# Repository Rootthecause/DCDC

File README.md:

Dear Formula Student Teams,

I've designed a High Voltage DC/DC Converter to replace our LV Battery. Feel free to use it as well!<br>
Although this design (and previous versions) have passed two times FSG scrutineering and have been operating without any issues for over 6 months, <strong>always manufacture at your own risk!</strong><br>
If you encountered any bugs or have suggestions for improvement, please use the GitHub [issues form](https://github.com/Rootthecause/DCDC/issues/new). For discussions and technical questions, kindly use the [discussion bord](https://github.com/Rootthecause/DCDC/discussions).<br> 

This design is published as open-source hardware under the CERN-OHL-W license and can be found on GitHub: https://github.com/Rootthecause/DCDC<br>
If you had early access to this GitHub page or received any files from me directly, please do not share or publish them, as I don't want others to share files which may be incomplete or contain errors.<br>

Have fun! Do not lick things with spark symbols on :) 

Best regards,
Rootthecause / Liv 

March 10, 2026: Thanks for giving this repro more than 100 stars! ⭐️
<br>

# Updates
### For recent updates on building a v9-3 replica, please read [the v9-3 Build Notes](https://github.com/Rootthecause/DCDC/blob/main/v9-3_build_notes.md).

|Date YYMMDD| Description |
|:---------------------:|:------|
|260812|**Urgent notice:** The distance between F1 and RV1 is too small, which can lead to a arc on the HV side while the DCDC is enabled. As long as both components do not touch each other conformal coating would prevent the insulation fault, however the actual spacing is influenced by mechanical tolerances. As a hotfix, isolating glue can be used to fill the gap and/or [low profile fuse clips](https://www.mouser.de/de/ProductDetail/576-01220090Z) (currently untested, should be less wide). The current spacings on the top copper layer between the components are sufficinet with conformal coating. More details on this issue will be added to the Build Notes soon.|
|260730| Currently used resonant C0G capacitors might cause converter failures. See [v9-3 Build Notes](https://github.com/Rootthecause/DCDC/blob/main/v9-3_build_notes.md) for more details.| 
|260609| Added new [v9-4_dev](https://github.com/Rootthecause/DCDC/tree/v9-4_dev) branch. This version is currently untested and not recommended for use. Some components were improved, like D14, U1, U11, Q8, Q9, Q10, Q11. SR FETs have more vias and 20% larger cooling surface. Increased TS side control voltage from 12V to 15V for lower conduction losses.|
|260326 | Update on [v10 development](https://github.com/Rootthecause/DCDC/discussions/9#discussioncomment-16319278) currently being slowed down due to transformer issues.|
|260314| Release of the v9-3r1.4 update. Fixes many smaller issues and probably issue #10. See [releases](https://github.com/Rootthecause/DCDC/releases) for more details.|
|260129| First public v10 schematic, see [v10 development](https://github.com/Rootthecause/DCDC/discussions/9#discussioncomment-15634156), also contains a timeline and small v9-3 update|
|260104| New year's update on [v10 development](https://github.com/Rootthecause/DCDC/discussions/9#discussioncomment-15400450) |
|251130| Update on [v10 development](https://github.com/Rootthecause/DCDC/discussions/9#discussioncomment-15114408), added  for faster communication.|
|250915| **IMPORTANT NOTICE**: There was a complaint about the converter not being rules conform. Due to other personal priorities it might take some weeks to solve the addressed points. There is also the chance of some points unable to be resolved for the Version 9-3r. See [issue#10](https://github.com/Rootthecause/DCDC/issues/10) for further details.|
|250806| Announcing the v10 development - ideas welcome! Read more [here](https://github.com/Rootthecause/DCDC/discussions/9). DCDCv10 [survey](https://forms.gle/ou8AZbYJj4cU9K3A8).|
|250718| A bad F_min setting lead to repeatable FET destruction, please re-read the Build Guide Pages 35/36 if you've set up your replica before this change. See [issue#8](https://github.com/Rootthecause/DCDC/issues/8) |
<br>

# Important documents
|File | | |
|:---------------------:|:--------------:|:------:|
| Documentation [PDF] | [ENGLISH](https://github.com/Rootthecause/DCDC/blob/main/documentation/Documentation_DCDCv9-3r_EN.pdf)| [GERMAN](https://github.com/Rootthecause/DCDC/blob/main/documentation/Documentation_DCDCv9-3r_GER.pdf) [Discontinued*]|
| Build Guide [PDF] | [ENGLISH](https://github.com/Rootthecause/DCDC/blob/main/documentation/Build_Guide_DCDCv9-3r_EN.pdf)| [GERMAN](https://github.com/Rootthecause/DCDC/blob/main/documentation/Build_Guide_DCDCv9-3r_GER.pdf) [Discontinued*]|
| Data sheet [PDF] | [ENGLISH](https://github.com/Rootthecause/DCDC/blob/main/documentation/Datasheet_DCDCv9-3.pdf)|-|
| KiCAD Files| [ENGLISH](https://github.com/Rootthecause/DCDC/tree/main/kicad)|-|
| Schematic [PDF] | [ENGLISH](https://github.com/Rootthecause/DCDC/blob/main/kicad/DCDCv9-3.pdf) |-|
| LTspice Simulation| [ENGLISH](https://github.com/Rootthecause/DCDC/tree/main/ltspice)|-|
| Measurements Table [xlsx] | [ENGLISH](https://github.com/Rootthecause/DCDC/blob/main/documentation/DCDCv9-3_Table.xlsx) |-|
| Scrutineering Support Presentation [PPTX] | [ENGLISH](https://github.com/Rootthecause/DCDC/blob/main/documentation/scrutineering_support_files/DCDCv9-3_Scrutineering_Support_Presentation.pptx)|-|

*will not be updated after the DCDCv9-3r1.4 release (March 14, 2026).

<br>

# Note for PCB-Orders
**Always check the latest release before ordering!**
There are new releases for every significant hardware change.
I do not recommend ordering from the latest repro clone, as it might contain unfinished hardware changes. However, simulation files or documents might be more recent.
<br>
<br>
# Who should build this?
This project is for anyone who is keen to build a DC/DC converter for powering low voltage devices from high voltages or for research.
Unfortunately, it's currently not a simple one-day-build (maybe 1-2 days for building and 1-2 Weeks for testing), but I'm working on it, making it as accessible as possible.
The skillset required ranges from soldering SMD components, SLA-Printing to sanding ferrite cores and winding a transformer (sanding is currently not needed anymore).
The documentation not only contains explanations of many components, but also detailed written assembly instructions.
I might also record a few instruction videos if there is a demand.
Stick with it - the results speak for themselves.<br>
<br>
# Technical Specifications

The DCDCv9-3 is a galvanically isolated DC/DC converter, designed to convert voltages from 200 V to 600 V down to 24 V with max. 500 W continuous output power. The low weight of 167 grams and the small footprint of a credit card (85.6 x 54 mm) are well suited to the automotive industry for supplying low-voltage systems from HV Batteries. The dynamic operating frequency between 90 and 200 kHz ensures high efficiency for various loads as well as good EMI compliance due to the resonant LLC soft switching topology. Customized versions allow output voltages from 12 V to 48 V.
<strong>

- Input Voltage Range: 200 to 600 V 
- Designed Output Voltage: 24 V
- max. Output Power (min. 400V):
	- Continous:&ensp;&ensp;&ensp;&ensp;500 W
	- 180 Seconds:&ensp; 600 W
	- 60 Seconds:&ensp;&ensp;&ensp;750 W
- max. continous Output Power at 200V: 300 W
- max. continous Output Power at 300V: 500 W
- Efficiency up to 96.9 % at 500 W load / 500 V input
- Size: 85.6 x 54 mm x 45 mm
- Weight: 167 grams

Features
- built-in solid-state precharge
- active rectification (NCP4305DMTTWG)
- Galvanically isolated enable pins with self recharging start-up capacitor
- undervoltage, overvoltage and overcurrent protection 
- low no-load power dissipation (7W-9W) 
- cost efficient UCC25600 LLC controller
- reliable 4 A/6 A UCC21520 Gate Driver
- onboard HV- and LV fuses
- minimum isolation distance 4.5 mm (According to rule EV 4.3.6, Table 5, Conformal Coating: 600V DC -> min. 4 mm spacing required)
- optional back side connectors for on-PCB mount 
- "FSG-Rules 2026 v1.1 conform", the complaint #10 was resolved in the v9-3r1.4 release. Teams were able to pass at FSCH, FSA, FSCZ in 2026 [more to come]. NOTE: As converters are manufactured by the teams with individual components (such as the HF-litz wire), they must be able to show e.g. isolation ratings. Without this, passing the technical inspection may be at the discretion of the scrutineer.
</strong>
<br>
<br>

### Future plans

The main goal of this project is to create a universal approach for safe and efficient conversion of voltages.
At the moment, the converter can accept any input voltage up to at least 600V if UVP/OVP and component
Values are chosen correctly. On the output side, the step-down regulator (65V) is the limiting factors. 
A VIPER06 IC could be used to achieve HV stepdown, or depending on the input voltage, 
the stepdown could be could be shifted to the input side. This could also allow a self-starting converter to 
be used as an SMPS in combination with a PFC. Another approach would be a bidirectional design so that the 
stepdown is on the lower voltage side. Since active rectification is already implemented, bidirectional 
conversion could be possible given the right IC. With the current development and rise of GaN MOSFETs, 
a converter with PCB transformer in the MHz range might also be possible.

# Do's and dont's 
## General
- Not as much as possible, but as much as needed (words from a friend).
- If you don't test to the limits, you don't know where they are.
- Always start with low Voltage/Power and slowly increase it.
- Figure out what measurements and values (step size) are important.
- If issues appear, try to solve them sooner than later - but depending on type, they can be an oppurtunity to test out limits.
- avoid making too many changes at once (except you want to perform multivariant testing), or be sure that the changes do not affect each other

## Project specific
- use short traces for anything that has to switch things (PCB design is complex, than that, but keep wire impedance low as well as parasitics)
- make sure, your gate Driver provides clean on-off signals to the MOSFETs. Otherwise you'll blow them up for sure sooner or later. Use MOSFETs with Kelvin connections if possible (and be sure about their correct wiring).
- Do use Gate driver IC's and not Gate Transformes (they suck). If possible, use Isolated Gate Drivers. Thats a good layer of protection if the half bridge blows up.
- Always have a Thermal Camera at hand. There are relatively cheap options as USB-C accessories for Phones (~250€). I use one from TOPDON with an added maco lens. It's worth every penny, not just for a DC/DC but also other FS Stuff. It will help you to find overloaded components (too hot) or non functioning compontens (no heat). Keep in mind, that there might be thermally reflective surfaces (brushed aluminium is like a mirror!). 
- Use your ears and nose in a quite environment while testing. Many issues can be heard (humming, cracking sounds), and some smelled (too hot component).
- Be sure to add test points to your PCB while developing, which can be acessed via jumper wires or simliar. Do not attempt to measure anything directly with a probe while the converter is running, since a small slip can be enough to ruin the whole converter and maybe even do harm to yourself. 
- use an Oscilloscope with Isolated inputs (alternative use differential probes or an battery powered Oscilloscope) to check signals. 

## Replicas
*Last updated: June 24, 2026*

- At least 4 Formula Student teams are replicating the DCDCv9-3r in 2026  
- At least 4 teams have successfully built and tested the DCDCv9-3r:  
  - TU Graz Racing, Austria, 2025 + 2026
  - Anonymous team, Germany, 2025
  - Anonymous team, Czech, 2025
  - Anonymous team, (modified version), England, 2026
  - Arrabona Racing Team, Hungary, 2026 
<br>

**Want to add your team to this list (publicly or anonymously)?**  
Send me a DM on [Reddit](https://www.reddit.com/user/Rootthecause/). 
Thanks! <br>

## Star History

<a href="https://www.star-history.com/?type=date&legend=bottom-right&repos=Rootthecause%2Fdcdc">
 <picture>
   <source media="(prefers-color-scheme: dark)" srcset="https://api.star-history.com/chart?repos=Rootthecause/dcdc&type=date&theme=dark&legend=bottom-right&sealed_token=mzjVnRIkla1vRBk2-KK44TFHBLLXQNpQxWfrkvZrKnmeYRq4vDsalk-4ebVN9e_loyW0JTCKtIhzX2gAzmecnIZoZ-mtmyZheD50UHvruGQUZOgHEQh1tdMgoWUtcaJrPUCjxlboJflvB1i19gqI4QuvRyrbwL13nwhyrt8bHj4ZewdpJkWvTW374E3O" />
   <source media="(prefers-color-scheme: light)" srcset="https://api.star-history.com/chart?repos=Rootthecause/dcdc&type=date&legend=bottom-right&sealed_token=mzjVnRIkla1vRBk2-KK44TFHBLLXQNpQxWfrkvZrKnmeYRq4vDsalk-4ebVN9e_loyW0JTCKtIhzX2gAzmecnIZoZ-mtmyZheD50UHvruGQUZOgHEQh1tdMgoWUtcaJrPUCjxlboJflvB1i19gqI4QuvRyrbwL13nwhyrt8bHj4ZewdpJkWvTW374E3O" />
   
 </picture>
</a>
<br>
<br>

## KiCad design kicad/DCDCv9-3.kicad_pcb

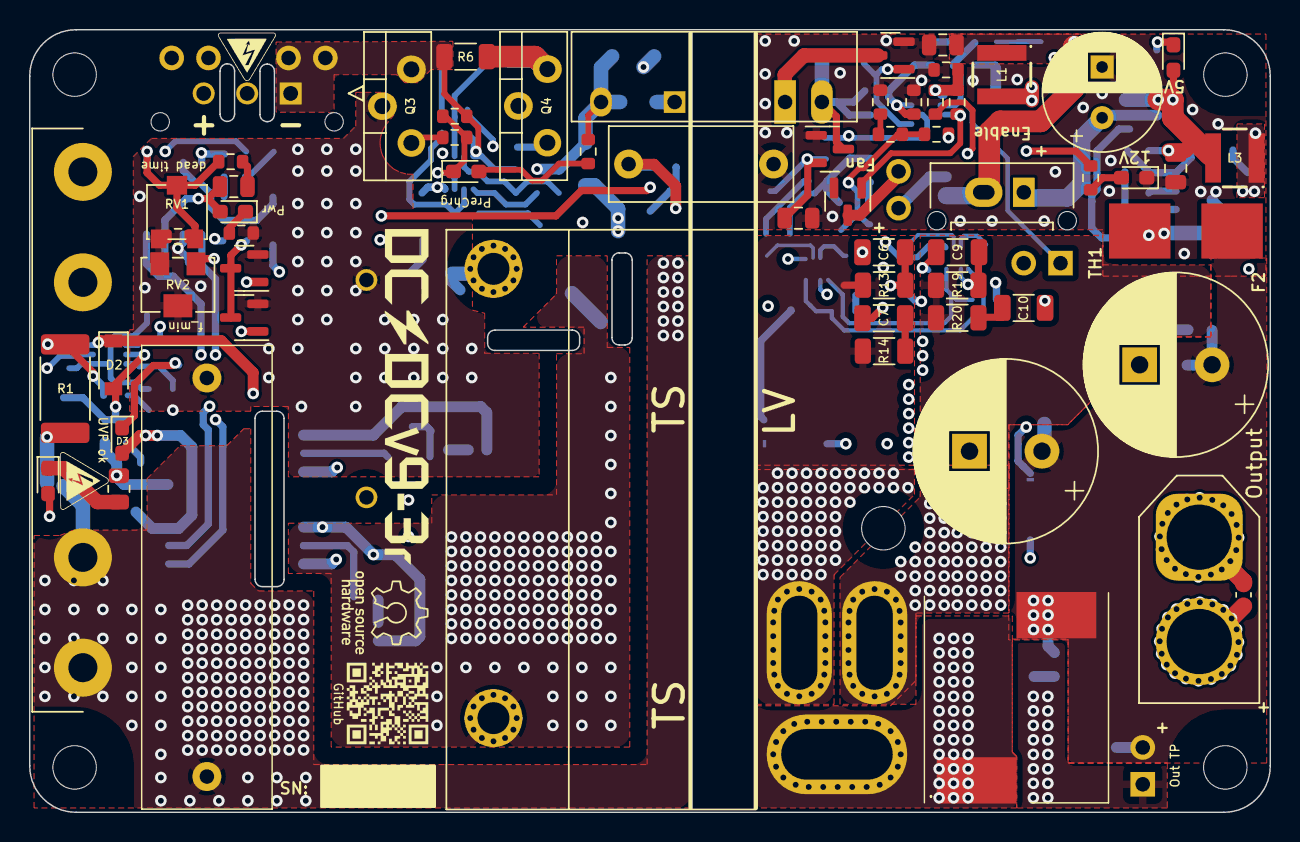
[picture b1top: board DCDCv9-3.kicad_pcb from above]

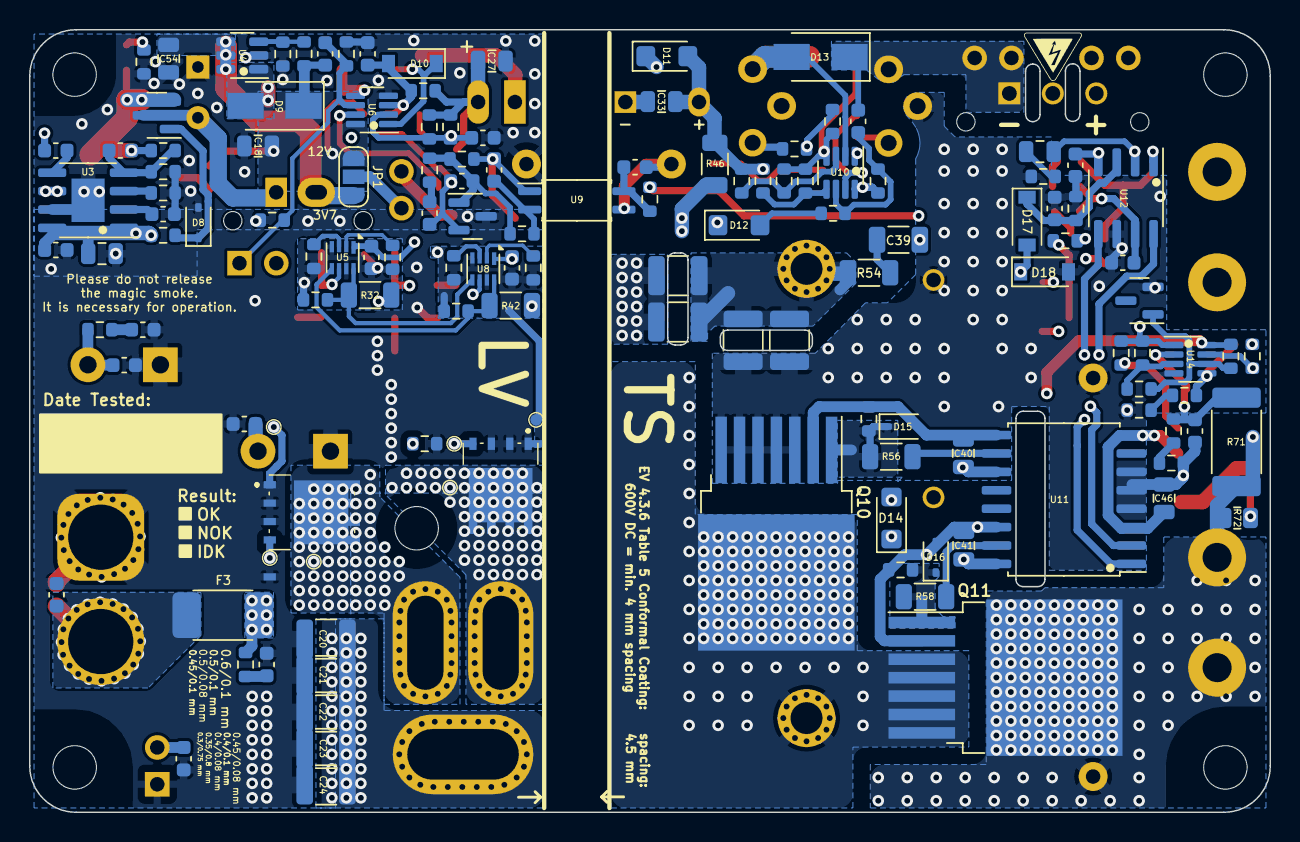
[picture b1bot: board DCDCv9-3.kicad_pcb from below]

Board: 4 copper layers, 85.6 x 54.0 mm, 208 parts (140 on the bottom side), 102 nets.

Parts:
C1: 2uF; MKP1848520704K2
C2, C15, C40, C41: 2.2uF; C_0805_2012Metric
C3: 22nF; R76UI22205050J
C4: 3.3nF; C_Disc_D12.5mm_W5.0mm_P10.00mm
C5, C33, C46: 10uF; C_0805_2012Metric
C6, C9: 1 nF; C_1206_3216Metric
C7, C10, C39: 470pF; C_1206_3216Metric
C8, C12, C18, C27, C42, C54: 22uF; C_0805_2012Metric
C11, C13: 2200uF; CP_Radial_D12.5mm_P5.00mm_symbol_inside
C14, C28: 100nF; C_0603_1608Metric
C16, C49, C50, C51, C52, C53, C55, C56, C57: 1nF; C_0603_1608Metric
C17, C19, C25, C31, C45: 1uF; C_0603_1608Metric
C20, C21, C22, C23, C24: 10uF; C_1210_3225Metric
C26, C44, C47: 22nF; C_0603_1608Metric
C29: 47pF; C_0603_1608Metric
C30, C32, C48: 10nF; C_0603_1608Metric
C34, C35, C36, C37: 5.6nF; C_1210_3225Metric
C38: 120pF; C_0603_1608Metric
C43: 470nF; C_0603_1608Metric
C_start1: 3.8V 25F Supercap; CP_Radial_D8.0mm_P3.50mm
D1: HV_Orange; LED_0603_1608Metric_Pad1.05x0.95mm_HandSolder
D2, D10, D17, D18: 1N4448; D_SOD-123
D3, D4, D5, D6, D7: Green; LED_0603_1608Metric_Pad1.05x0.95mm_HandSolder
D8, D15, D16: CDSOD323-T12; D_SOD-323
D9, D13: SS1H10; D_SMA
D11, D12, D14: VS-E7FX0212-M3/I; D_SMF
F1: 1.6A; Fuseholder0,25Zoll_32mm_littlefuse_102_122
F2: 500mA; NANO-0154-OMNI-BLOK-Fuse-Holder
F3: 20A; Bel_SMCF_Fuse_2410_6125Metric
HV_Logo_1, HV_Logo_1#2, HV_Logo_1#3: HV_Logo_1; HV_Logo_small
J1: 43650-0315; 43650-03YY_151617
J2, J4, J6, J7, J8: Conn_01x02_Male; PinHeader_1x02_P2.54mm_Vertical
J3: Conn_01x02; Molex_Micro-Fit_3.0_43650-0215_1x02_P3.00mm_Vertical_combin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
J5: XT60 Male; AMASS_XT60-F_1x02_P7.20mm_Vertical
JP1: Fan Voltage Select; SolderJumper-3_P1.3mm_Open_RoundedPad1.0x1.5mm_NumberLabels
L1: 4.7uH; ASPI-4030S
L2: 1uH; 7443091100_v9.2
L3: 10uH; ASPI-4030S
NT1, NT2: NetTie_2; dummy_net_line_0.5mm
Q1, Q2, Q5, Q6, Q7: PMV20ENR; SOT-23
Q3: SIHP24N80AE-GE3; TO-220-3_Vertical_HV1.2mm
Q4: IXYP8N90C3; TO-220-3_Vertical_HV1.2mm
Q8, Q9: BSC027N06LS5ATMA1
Q10, Q11: IMBG65R050M2HXTMA1; TO-263-7_TabPin8
QR_Coode_1: QR_Coode; GitHub_QR_Code
R1, R71: 100M; R_2512_6332Metric_Pad1.40x3.35mm_HandSolder
R2, R72: 330k; R_0805_2012Metric
R3: 3.0k; R_0603_1608Metric
R4, R39, R41, R59, R61: 1k; R_0603_1608Metric
R5, R7, R9, R11, R15, R16, R21, R23, R30, R33, R40, R43, R51, R52, R55, R57, R63: 10k; R_0603_1608Metric
R6, R14, R20: 47; R_1206_3216Metric
R8, R10, R22, R29, R38, R48, R49: 2.2k; R_0603_1608Metric
R12: 910; R_0603_1608Metric
R13, R19: 100; R_1206_3216Metric
R17, R24: 27k; R_0603_1608Metric
R18, R27, R50: 470k; R_0603_1608Metric
R25: 240k; R_0603_1608Metric
R26, R45, R47, R53, R67, R70, R75: 100k; R_0603_1608Metric
R28, R34, R66: 33k; R_0603_1608Metric
R31, R36: 4.7k; R_0603_1608Metric
R32, R42: 4.7; R_1206_3216Metric
R35: 330k; R_0603_1608Metric
R37: 47k; R_0603_1608Metric
R44: 510; R_0603_1608Metric
R46: 20; R_1206_3216Metric
R54: 10M; R_1206_3216Metric
R56, R58: 10; R_1206_3216Metric
R60: 82k; R_0603_1608Metric
R62, R69: 100M; R_0603_1608Metric
R64: 820k; R_0603_1608Metric
R65: 510k; R_0603_1608Metric
R68: 1.6M; R_0603_1608Metric
R73, R74: 10; R_0603_1608Metric
RV1: 20k; Potentiometer_Bourns_PVG3G
RV2: 10k; Potentiometer_Bourns_3214W_Vertical
T1: DIY Transformer ETD 39; Transformer_ETD39_uprightV3.6 (PSS 24V)
TH2: 1k PTC; R_0603_1608Metric
TP1, TP2, TP3, TP4, TP5, TP6: TestPoint; TestPoint_Pad_D0.8mm_DC-DC
TP8: GaN GND2; TestPoint_Pad_D0.8mm_DC-DC
U1: RP-1212S; Converter_DCDC_TRACO_TBA 1-1212HI-3kV-iso
U2: RT9058-90GVL; SOT-23
U3: MP4541_SOP8-EP; SOIC-8-1EP_3.9x4.9mm_P1.27mm_EP2.29x3mm XL7005
U4: TLV61048DBVR; SOT-23-6
U5, U8: NCP4305DMTTWG; WDFN-8_2x2mm_P0.5mm
U6, U10, U14: LM2904BIDDFR; SOT-23-8_DC-DC_v9
U7: TL431BCDBZR; SOT-23
U9: ACPL-217-50AE; SOIC-4_4.55x2.6mm_P1.27mm
U11: UCC21520DW; SOIC-16W_7.5x10.3mm_P1.27mm
U12: UCC25600; SOIC-8_3.9x4.9mm_P1.27mm
U13: ZXRE330ASA-7; SOT-23

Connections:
24V_TP: C11.1, C13.1, C50.2, C51.2, C52.2, F2.1, F3.1, J4.1, L2.2, R17.1, R73.1, R74.1
+3V7: C8.1, C54.1, J3.2, JP1.3 (B), L1.1, U4.4 (~SHDN), U4.5 (IN), U4.6 (nc)
+9V: C5.1, C30.2, R39.1, U2.2 (VO), U9.1
+12V_HS: C41.2, D14.1 (K), U11.16 (VDDA)
+12V_IN: C2.2, C40.2, C45.2, C46.1, D2.1 (K), D3.2 (A), D4.2 (A), D11.1 (K), R70.1, U11.3 (VCCI), U11.8 (VCCI), U11.11 (VDDB), U12.7 (VCC), U14.8 (V+)
+12V_sw: C18.1, C19.2, C25.1, C27.1, C31.1, D9.1 (K), J8.1, JP1.1 (A), R16.1, R21.2, R27.1, R34.1, R35.2, R36.2, U1.1 (+VIN), U2.3 (VI), U5.1 (VCC), U6.8 (V+), U8.1 (VCC)
+24V: C15.2, C53.2, F2.2, R26.2, U3.1 (EN), U3.8 (VIN)
+HV: C1.2, C34.1, C35.1, F1.2, Q11.8 (D), R1.1, R71.1, R72.1
+HV_in: F1.1, J1.3, J7.1, J7.2
-HV_in: C33.2, C38.1, D13.1 (K), J1.1, J6.1, J6.2, Q3.3 (S), R6.2, R7.2, R48.1, R50.1, R51.2, U1.5 (-VOUT), U10.4 (V-)
-HV_pc: C1.1, C3.2, C4.1, C32.2, C36.2, C37.2, C43.2, C44.1, C45.1, C46.2, C47.2, D12.1 (K), D18.2 (A), Q1.2 (S), Q2.2 (S), Q3.2 (D), Q4.2 (C), Q10.3 (S), Q10.4 (S), Q10.5 (S), Q10.6 (S), Q10.7 (S), R2.2, R3.2, R5.1, R59.2, R60.1, R65.2, R68.2, RV1.3, RV2.2, RV2.3, U9.3, U11.4 (GND), U11.5 (DIS), U11.6 (DT), U12.6 (GND), U13.2, U14.4 (V-)
/HB_out: Q10.8 (D), Q11.3 (S), Q11.4 (S), Q11.5 (S), Q11.6 (S), Q11.7 (S), T1.1 (AA)
/HS: U11.1 (INA), U12.8 (GD1)
/LS: U11.2 (INB), U12.5 (GD2)
/OC: C44.2, D17.1 (K), R60.2, U12.3 (OC)
/OTP_FAN: Q5.1 (G), R18.1, U6.7
/OTP_OFF: D10.1 (K), Q6.1 (G), U6.1
/OVP: Q2.1 (G), R69.1, U14.7
/Opc+: C32.1, R44.2, U9.4
/Synchronous Rectification/3: Q9.5 (D_1), Q9.6 (D_2), Q9.7 (D_3), Q9.8 (D_4), Q9.9 (D_5), R13.2, R14.1, T1.3 (SB), TP5.1
/Synchronous Rectification/5: Q8.5 (D_1), Q8.6 (D_2), Q8.7 (D_3), Q8.8 (D_4), Q8.9 (D_5), R19.2, R20.1, T1.5 (SA), TP3.1
/UVP: Q1.1 (G), R62.1, R63.1, U14.1
GND: C4.2, C5.2, C7.1, C8.2, C10.1, C11.2, C12.1, C13.2, C15.1, C17.1, C18.2, C20.2, C21.2, C22.2, C23.2, C24.2, C27.2, C28.1, C48.1, C49.1, C50.1, C51.1, C52.1, C53.1, C54.2, C55.1, C56.1, C57.1, C_start1.2 (-), D6.1 (K), D8.2 (A2), J4.2, J5.2, NT1.2, NT2.2, Q5.2 (S), Q6.2 (S), Q8.1 (S_1), Q8.2 (S_2), Q8.3 (S_3), Q9.1 (S_1), Q9.2 (S_2), Q9.3 (S_3), R10.2, R11.2, R15.1, R22.1, R23.2, R25.1, R28.2, R31.1, R75.2, TH2.2, TP8.1, U2.1 (GND), U3.7 (GND), U4.2 (GND), U6.4 (V-), U7.3 (A)
unnamed: C2.1, R4.2
unnamed: C7.2, R14.2
unnamed: C10.2, R20.2
unnamed: C26.2, R37.1
unnamed: C30.1, R41.1, U9.2
unnamed: C39.2, R54.1
unnamed: C42.2, R59.1
unnamed: C56.2, R73.2
unnamed: C57.2, R74.2
unnamed: C_start1.1 (+), J3.1, Q7.3 (D)
unnamed: D1.2 (A), R72.2
unnamed: D1.1 (K), R2.1
unnamed: C47.1, D2.2 (A), R67.2, R71.2, U14.2 (-)
unnamed: D3.1 (K), R63.2
unnamed: D4.1 (K), R5.2
unnamed: D5.2 (A), R9.1
unnamed: D5.1 (K), R7.1, R8.2, U10.7
unnamed: D6.2 (A), R21.1
unnamed: C12.2, C16.2, D7.2 (A), L3.2, Q7.2 (S), R24.1
unnamed: D7.1 (K), R22.2
unnamed: D8.1 (A1), Q7.1 (G), R26.1
unnamed: D9.2 (A), L1.2, U4.1 (SW)
unnamed: C48.2, D10.2 (A), R11.1, R34.2, U6.3 (+)
unnamed: C33.1, D11.2 (A), R9.2, R45.2, R46.2, R47.2, R53.2, U1.7 (+VOUT), U10.8 (V+)
unnamed: D12.2 (A), R52.1
unnamed: D13.2 (A), Q4.3 (E), R6.1, U10.2 (-)
unnamed: D14.2 (A), R46.1
unnamed: D15.1 (A1), Q10.1 (G), R55.1, R56.1
unnamed: C40.1, D15.2 (A2), Q10.2 (DS), R55.2, U11.9 (VSSB)
unnamed: D16.1 (A1), Q11.1 (G), R57.1, R58.1
unnamed: C41.1, D16.2 (A2), Q11.2 (DS), R57.2, U11.14 (VSSA)
unnamed: C39.1, D17.2 (A), D18.1 (K)
unnamed: J2.1, JP1.2 (C)
unnamed: J2.2, Q5.3 (D)
unnamed: C49.2, C55.2, F3.2, J5.1
unnamed: C19.1, J8.2, R31.2, R75.1, U6.6 (-)
unnamed: Q1.3 (D), Q2.3 (D), R61.1
unnamed: Q3.1 (G), R8.1
unnamed: Q4.1 (G), R49.1
unnamed: Q8.4 (G), R32.1, TP2.1
unnamed: Q9.4 (G), R42.1, TP4.1
unnamed: R10.1, R12.2
unnamed: R49.2, R51.1, U10.1
unnamed: R65.1, R66.2
unnamed: R67.1, R68.1
unnamed: C34.2, C35.2, C36.1, C37.1, R54.2, T1.2 (AB)
unnamed: C20.1, C21.1, C22.1, C23.1, C24.1, L2.1, T1.4 (SC)
unnamed: C14.2, U3.5 (BST)
unnamed: C16.1, R23.1, R24.2, U3.4 (FB)
unnamed: R25.2, U3.3 (FREQU)
unnamed: C14.1, L3.1, U3.6 (SW)
unnamed: C17.2, U3.2 (VCC)
unnamed: R27.2, R28.1, U4.3 (FB)
unnamed: C9.2, R19.1, U5.6 (CS)
unnamed: R30.2, R32.2, U5.8 (DRV), U8.5 (TRIG/DIS)
unnamed: C9.1, C25.2, NT1.1, R29.1, R30.1, R33.1, TP1.1, U5.4 (LLD), U5.7 (GND)
unnamed: R33.2, U5.2 (MIN_TOFF)
unnamed: R29.2, U5.3 (MIN_TON)
unnamed: R40.2, R42.2, U5.5 (TRIG/DIS), U8.8 (DRV)
unnamed: C28.2, R35.1, R36.1, TH2.1, U6.2 (-)
unnamed: R15.2, R16.2, R18.2, U6.5 (+)
unnamed: C29.2, R37.2, R39.2, R41.2, U7.1 (K)
unnamed: C26.1, C29.1, R12.1, R17.2, U7.2 (REF)
unnamed: C6.2, R13.1, U8.6 (CS)
unnamed: C6.1, C31.2, NT2.1, R38.1, R40.1, R43.1, TP6.1, U8.4 (LLD), U8.7 (GND)
unnamed: R43.2, U8.2 (MIN_TOFF)
unnamed: R38.2, U8.3 (MIN_TON)
unnamed: R45.1, R48.2, U10.3 (+)
unnamed: R47.1, R50.2, U10.5 (+)
unnamed: C38.2, R52.2, R53.1, U10.6 (-)
unnamed: R58.2, U11.15 (OUTA)
unnamed: R56.2, U11.10 (OUTB)
unnamed: R3.1, R4.1, RV1.1, RV1.2, U12.1 (DT)
unnamed: C42.1, R44.1, RV2.1, U12.2 (RT)
unnamed: C43.1, R61.2, U12.4 (SS)
unnamed: R62.2, R64.1, U14.3 (+)
unnamed: R1.2, R66.1, R69.2, U14.5 (+)
unnamed: R64.2, R70.2, U13.1, U14.6 (-)
OTP_FET: Q6.3 (D), U1.2 (-VIN)

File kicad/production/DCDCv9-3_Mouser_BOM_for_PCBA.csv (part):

Reference,Value,Datasheet,Manufacturer_Part_Number,Footprint,Qty,DNP,ignore for PCBA,ignore for iBom,Description,comment,Source
C_start1,3.8V 25F Supercap,https://www.mouser.de/ProductDetail/Cornell-Dubilier-CDE/VMF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,VMF256M3R8,DCDC-Footprints:CP_Radial_D8.0mm_P3.50mm,1,,1,,,,Mouser
C1,2uF,https://www.mouser.de/ProductDetail/Vishay-Roederstein/MKP18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,MKP1848520704K2,DCDC-Footprints:MKP1848520704K2,1,,1,,"2F Film Capacitor 700V Polypropylene (PP), Metallized Radial",,Mouser
"C11,C13",2200uF,https://www.mouser.de/ProductDetail/Nichicon/UHW1V222MHD?qs=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,UHW1V222MHD,DCDC-Footprints:CP_Radial_D12.5mm_P5.00mm_symbol_inside,2,,1,,,,Mouser
"C20,C21,C22,C23,C24",10uF,https://www.mouser.de/ProductDetail/Murata-Electronics/GRM32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,GRM32ER71J106MA12L,DCDC-Footprints:C_1210_3225Metric,5,,,1,,,Mouser
C3,22nF,https://www.mouser.de/ProductDetail/80-R76UI22205050J,R76UI22205050J,DCDC-Footprints:R76UI22205050J,1,DNP,1,1,"R76, Film, Double Metallized Polypropylene, Automotive Grade, 0.022 uF, 5%, 2000 VDC, 85C, Lead Spacing = 15mm",,Mouser
"C34,C35,C36,C37",5.6nF,https://www.mouser.de/ProductDetail/KEMET/C1210C562JDGACAUTO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,C1210C562JDGACAUTO,DCDC-Footprints:C_1210_3225Metric,4,,1,,,,Mouser
C4,3.3nF,https://www.mouser.de/ProductDetail/Vishay-BC-Components/VY1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,VY1332M59Y5UQ63V0,DCDC-Footprints:C_Disc_D12.5mm_W5.0mm_P10.00mm,1,,1,,,,Mouser
"C5,C33,C46",10uF,https://www.mouser.de/ProductDetail/Taiyo-Yuden/TMK212BBJ106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,TMK212BBJ106KG-T,DCDC-Footprints:C_0805_2012Metric,3,,,1,,,Mouser
D1,HV_Orange,https://www.mouser.de/ProductDetail/Kingbright/APTD1608LSECK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,APTD1608LSECK/J4-PF,DCDC-Footprints:LED_0603_1608Metric_Pad1.05x0.95mm_HandSolder,1,,,1,,,Mouser
"D11,D12,D14",VS-E7FX0212-M3/I,https://www.mouser.de/ProductDetail/Vishay/VS-E7FX0212-M3-I?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, VS-E7FX0212-M3/I,DCDC-Footprints:D_SMF,3,,1,,,,Mouser
"D3,D4,D5,D6,D7",Green,https://www.mouser.de/ProductDetail/Inolux/IN-S63AT5G?qs=fAH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,IN-S63AT5G,DCDC-Footprints:LED_0603_1608Metric_Pad1.05x0.95mm_HandSolder,5,,,1,,,Mouser
F1,1.6A,https://eu.mouser.com/ProductDetail/Bel-Fuse/0ADBC1600-BE?qs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,0ADBC1600-BE ,"DCDC-Footprints:Fuseholder0,25Zoll_32mm_littlefuse_102_122",1,,1,,,Fuse weight: ceramic variant: 3.04 g,Mouser
"F1.1,F1.2",~,https://www.mouser.de/ProductDetail/Littelfuse/01220083Z?qs=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,01220083Z,~,2,,,,,,Mouser
F2,500mA,https://www.mouser.de/ProductDetail/Littelfuse/0154.500DR?qs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,0154.500DR,DCDC-Footprints:NANO-0154-OMNI-BLOK-Fuse-Holder,1,,1,,,,Mouser
F3,20A,https://www.mouser.de/ProductDetail/Bel-Fuse/0679L9200-01?qs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,0679L9200-01,DCDC-Footprints:Bel_SMCF_Fuse_2410_6125Metric,1,,1,,,Weight: 0.12g,Mouser
J1,Screw_Terminal_01x03,https://www.mouser.de/ProductDetail/TE-Connectivity/282828-2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,282828-2,DCDC-Footprints:TerminalBlock_TE-282817-2_1x03_P5.00mm_90 Degrees updated v9-3,1,,1,,,Do not install if clip-on installation is used. Use J6 and J7 instead,Mouser
J1.1,Screw_Terminal_01x03,https://www.mouser.de/ProductDetail/TE-Connectivity/284051-2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,284051-2,~,1,,1,,HV Plug angled,use J1.1 or J1.2 (order both just in case),Mouser
J1.2,Screw_Terminal_01x03,https://www.mouser.de/ProductDetail/TE-Connectivity/282809-2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,282809-2,~,1,,1,,HV Plug straight,use J1.1 or J1.2 (order both just in case),Mouser
"J2,J4,J8",Conn_01x02_Male,https://www.mouser.de/ProductDetail/Molex/42375-2486?qs=ZGcr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,42375-2486,DCDC-Footprints:PinHeader_1x02_P2.54mm_Vertical,3,,1,,,,Mouser
J3,Conn_01x02,https://www.mouser.de/ProductDetail/Molex/43650-0215?qs=Aplf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,43650-0215,DCDC-Footprints:Molex_Micro-Fit_3.0_43650-0215_1x02_P3.00mm_Vertical_combined2.54pinheader,1,,1,,,"switch must handle at least 0.5 A, Do not install if clip-on installation is used, install a 2.54 mm Pin header on the bottom side instead",Mouser
J3.1,Conn_01x02,https://www.mouser.de/ProductDetail/Molex/43645-0200?qs=4XSM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,43645-0200,,1,,1,,Receptacle Housing,Receptacle Housing,Mouser
"J3.2,J3.3",Conn_01x01_Pin,https://www.mouser.de/ProductDetail/Molex/35044-9102?qs=ZlMU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,35044-9102,~,2,,,,Crimp for molex micofit receptacle housing,,
J5,XT60 Male,https://www.amazon.de/RUNCCI%C2%AE-Connector-M%C3%A4nnlich-W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,~,DCDC-Footprints:AMASS_XT60-F_1x02_P7.20mm_Vertical,1,,1,,,install on the top or bottom depending on normal or clip-on mount,Amazon
J5.1,XT60 Female (wrong symbol ik),https://www.amazon.de/RUNCCI%C2%AE-Connector-M%C3%A4nnlich-W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,~,~,1,,1,,Female,for connecting your LV System to the DCDC,Amazon
"J6,J7",Conn_01x02_Male,https://www.mouser.de/ProductDetail/Molex/42375-2486?qs=ZGcr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,42375-2486,DCDC-Footprints:PinHeader_1x02_P2.54mm_Vertical,2,DNP,1,1,,,Mouser
JP1,Fan Voltage Select,~,~,DCDC-Footprints:SolderJumper-3_P1.3mm_Open_RoundedPad1.0x1.5mm_NumberLabels,1,,1,,,Bridge the middle pad with solder to one of the outer pads for voltage selection. Standard: 3V7. It's not implied to put a component on here.,-
L1,4.7uH,https://www.mouser.de/ProductDetail/ABRACON/ASPI-4030S-4R7M-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,ASPI-4030S-4R7M-T,DCDC-Footprints:ASPI-4030S,1,,1,,Fixed Inductors 4.7uH 20% Shielded -40C +125C,,Mouser
L2,1uH,https://www.mouser.de/ProductDetail/Wurth-Elektronik/7443091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,7443091100,DCDC-Footprints:7443091100_v9.2,1,,1,,,,Mouser
L3,10uH,https://www.mouser.de/ProductDetail/ABRACON/ASPI-4030S-100M-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,ASPI-4030S-100M-T,DCDC-Footprints:ASPI-4030S,1,,1,,Fixed Inductors 10uH 20% Shielded -40C +125C,,Mouser
M1,Fan,https://www.amazon.de/gp/product/B071JN6HKM/,~,DCDC-Footprints:PinHeader_1x02_P2.54mm_Vertical,1,,,,Fan,,Amazon
"Q10,Q11",IMBG65R050M2HXTMA1,https://www.mouser.de/ProductDetail/Infineon-Technologies/IM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,IMBG65R050M2HXTMA1,DCDC-Footprints:TO-263-7_TabPin8,2,,1,,,,Mouser
Q3,SIHP24N80AE-GE3,https://www.mouser.de/ProductDetail/Vishay-Siliconix/SIHP24N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,SIHP24N80AE-GE3,DCDC-Footprints:TO-220-3_Vertical_HV1.2mm,1,,1,,,,Mouser
Q4,IXYP8N90C3,https://www.mouser.de/ProductDetail/IXYS/IXYP8N90C3?qs=INK05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,IXYP8N90C3,DCDC-Footprints:TO-220-3_Vertical_HV1.2mm,1,,1,,,,Mouser
RV1,20k,https://www.mouser.de/ProductDetail/Bourns/PVG3A203C01R00?qs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,PVG3A203C01R00,DCDC-Footprints:Potentiometer_Bourns_PVG3G,1,,,1,,"set dead time, R3 can be used for a fixed value. Should be set at highest input voltage and no load.",Mouser
RV2,10k,https://www.mouser.de/ProductDetail/Bourns/PVG5A103C03R00?qs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,PVG5A103C03R00,DCDC-Footprints:Potentiometer_Bourns_3214W_Vertical,1,,,1,,"used to set minimum switching freqeuncy, should be adjusted to around 2-5 kHz above no-load resonant freqeuncy",Mouser
T1,DIY Transformer ETD 39,https://www.mouser.de/ProductDetail/EPCOS-TDK/B66363G0000X19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,B66363G0000X197,DCDC-Footprints:Transformer_ETD39_uprightV3.6 (PSS 24V),1,,1,,,"see Documentation chapter ""Transformer""",Mouser
T1.1,Ferrite Core,https://www.mouser.de/ProductDetail/871-B66363GX197,B66363G0000X197,~,1,,1,,N97 Core without air gap,N97 Core without air gap,Mouser
T1.2,Ferrite Core (gapped),https://www.mouser.de/ProductDetail/EPCOS-TDK/B66363G1000X12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,B66363G1000X127,~,1,,1,,N97 Core without air gap,N97 Core without air gap,Mouser
T1.3,1800 mm 120 x 0.1 mm HF litz wire (Prim),https://www.ebay.de/itm/304154052959?_skw=hf+litze&itmmeta=0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,120 x 0.1 mm,~,1,,,,"Inductor, rotated by 45°",HF litz wire,Ebay
"T1.4,T1.5","165 mm 600 x 0,071 mm HF litz wire (inner Sec)",https://www.ebay.de/itm/304154052959?_skw=hf+litze&itmmeta=0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,120 x 0.1 mm,~,2,,,,"Inductor, rotated by 45°",HF litz wire,Ebay
TH1,3.9k PTC (read build guide!),https://www.mouser.de/ProductDetail/Vishay-Dale/TFPTL15L3901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,TFPTL15L3901FL2B,DCDC-Footprints:PinHeader_1x02_P2.54mm_Vertical,1,,1,,,"if disconnected, fan will be on permanently (can be a desired feature), mount according to build guide",Mouser
TH2,1k PTC,https://www.mouser.de/ProductDetail/Vishay-Dale/TFPT0603L100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,TFPT0603L1001DV,DCDC-Footprints:R_0603_1608Metric,1,,1,,,"max. 1 kΩ for 0603 size available, but higher resistance would be better for SNR and lower current",Mouser
U1,TBA 1-1212HI,https://www.mouser.de/ProductDetail/TRACO-Power/TBA-1-1212HI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,TBA 1-1212HI,DCDC-Footprints:Converter_DCDC_TRACO_TBA 1-1212HI-3kV-iso,1,,1,,PEME1-S12-S12-S has lower current consumption but is out of stock,,Mouser
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
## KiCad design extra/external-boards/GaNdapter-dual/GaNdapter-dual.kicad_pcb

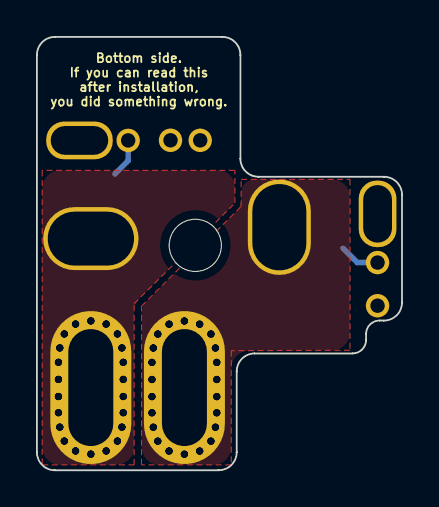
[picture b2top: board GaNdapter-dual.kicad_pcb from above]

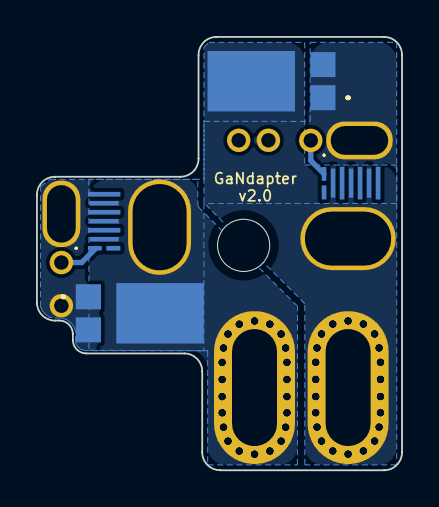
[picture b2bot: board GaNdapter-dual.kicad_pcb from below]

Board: 2 copper layers, 20.3 x 24.1 mm, 12 parts (4 on the bottom side), 5 nets.

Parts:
D1, D2: SBR10U200P5-13; SBR10U200P513
Q3, Q4: GAN3R2-100CBEAZ; GAN3R2100CBEAZ
TP1, TP11: TestPoint; GanDapter Long pad
TP2, TP5: TestPoint; GanDapter short pad
TP3, TP12, TP13, TP14: TestPoint; GanDapter single pad

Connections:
/Synchronous Rectification/3: D1.3 (K), Q3.3 (D), Q3.5 (D), Q3.7 (D), TP1.1
/Synchronous Rectification/5: D2.3 (K), Q4.3 (D), Q4.5 (D), Q4.7 (D), TP11.1
GND: D1.1 (A_1), D1.2 (A_2), D2.1 (A_1), D2.2 (A_2), Q3.2 (S), Q3.4 (S), Q3.6 (S), Q3.8 (S), Q4.2 (S), Q4.4 (S), Q4.6 (S), Q4.8 (S), TP2.1, TP5.1, TP14.1
unnamed: Q4.1 (G), TP12.1
unnamed: Q3.1 (G), TP3.1

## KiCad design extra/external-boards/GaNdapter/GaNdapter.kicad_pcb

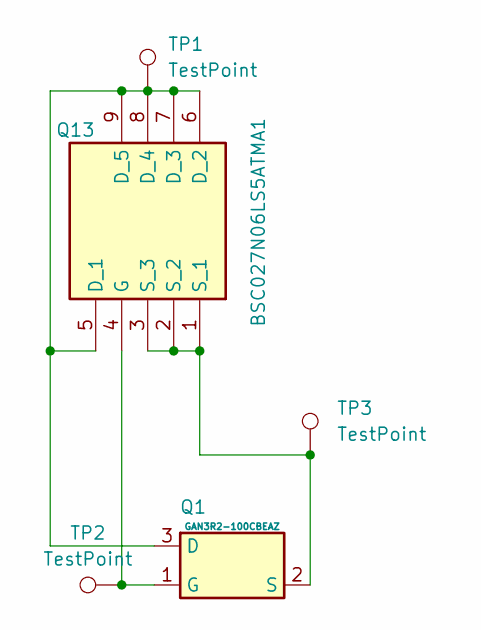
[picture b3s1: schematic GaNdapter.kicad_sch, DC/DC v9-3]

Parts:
Q1: GAN3R2-100CBEAZ; GAN3R2100CBEAZ; Mouser Part Number 771-GAN3R2-100CBEAZ
Q13: BSC027N06LS5ATMA1; Mouser Part Number 726-BSC027N06LS5ATMA
TP1: TestPoint; GanDapter Long pad
TP2: TestPoint; GanDapter single pad
TP3: TestPoint; GanDapter short pad

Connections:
unnamed: Q1.1 (G), Q13.4 (G), TP2.1
unnamed: Q1.3 (D), Q1.5 (D), Q1.7 (D), Q13.5 (D_1), Q13.6 (D_2), Q13.7 (D_3), Q13.8 (D_4), Q13.9 (D_5), TP1.1
unnamed: Q1.2 (S), Q1.4 (S), Q1.6 (S), Q1.8 (S), Q13.1 (S_1), Q13.2 (S_2), Q13.3 (S_3), TP3.1

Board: 2 copper layers, 5 parts (0 on the bottom side), 3 nets, no tracks yet.

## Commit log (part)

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2025-01-27 updated readme, removed copy of some pictures
2025-01-27 adjusted creepage distance
    The closest inner layer to outer layer, which uses a prepreg of 0.21 mm, would result in 0.81 mm creepage distance on edges. Due to unknown IPC 2221 rating for this case, the design was adjusted (bel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
2025-01-28 rm unused symbol lib, rm factual error about saturation losses in doc
2025-01-28 fixed typo in README.md
2025-01-28 fixed typo
2025-02-04 improved clearance on R54
2025-02-04 increased clearance a bit more
2025-02-11 increased distances on Coil formers
    Increased distances on Coil formers. Width changed from 22 mm to 26 so 2 mm more on each side. This increases creepage distance to at least 4 mm (realistically it's more than 6 mm) and adding more ma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
2025-02-19 fixed paragraph which was still in german
2025-03-08 included LTspice simulation for precharge
2025-03-08 updated PCBA BOM due to JLC error
2025-03-14 updated simulation files to better represent real life control loop behavior
2025-03-16 fixed mixed up U_on/off comment at U6B, added PDF plot of schematic, replaced TL431 ED back to TL431
2025-03-16 updated Readme.md with better formatting
2025-03-16 Improved Readme formatting
2025-03-17 added inductance calculator with air gap to table
2025-03-20 added transformer calc for LTspice
2025-04-23 updated bom, wrong 22uF cap for 0805 footprint
2025-05-01 fixed wrong gate charge in LTspice FET Model
    Ut was set to 2200 nC but should be 22 nC. Seems to not affect much in the simulation.
2025-05-04 LTSpice Models: wrong inductor resistance, changed 12V version capacitance
2025-05-09 updated readme with Replicas section
2025-05-17 Changed Mounting Holes from 2.9 mm to 3.0 mm
    Changed Mounting Holes from 2.9 mm to 3.0 mm. Although 2.9 mm was a nice fit for M3 screws, increasing it a bit will help against manufacturing tolerances.
    Note: The footprint originated from a M2.5 Footprint. Despite changing the diameter, the old name remained until now.
    Rules note: T 10.1.2 does not apply (Minimum M4), als the DCDC is not part of any primary structure. However, if somebody really needs M4, it is totally possible to increase the hole size by drilling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
2025-05-21 Update May 21 2025
    - Updated all Docs, for details see Revision History (new) on last page
    - added STEP files in addition to the STL for Transformer parts
    - fixed components on Mouser_BOM_for_PCBA despite being already placed on the PCBA, added UCC25600 for PCBA
2025-05-22 updated Table, see revision history on the first table page
2025-06-11 Added note about not using 24 V on the output for testing
    Added note about not using 24 V on the output for testing due to the control loop shutting down the converter (which must happen - but is not useful for tests).
2025-06-19 Added R75 to lower the fan turn-on temperature
    Note: R75 (100k) is not added in the PCB design due to space restrictions. It is paralleled to R31 (4.7k) so the parallel value is around 4.49 k. The turn-on temperature is now 72°C and turn-off 58°C.
    The original design was measured to have 71°C/61°C on/off. However it was found that when mounted, the transformer could reach 90°C on the top without turning on the fan. A new measurement showed, th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
2025-06-23 updated Build guide
    Added notes about secondary coil being swapped and enable switch having too high resistance, added more details about IR-Thermometers measurement issues.
2025-06-24 Update README.md
    Added note about first failure
2025-06-26 fixed typo about CW or CCW turning direction of f_min in the German Build Guide only (english was ok)
2025-06-29 Important update: Changed Gate Resistors
    R58 and R56 have been changed due to slight overvoltage. Deadtime must be increased to at least 150 ns (turn RV1 CCW). For more details see release notes DCDCv9-3r1.3
2025-07-05 Added WARNING to README (see issue), added Schematic as PDF
    Issue see: https://github.com/Rootthecause/DCDC/issues/8
2025-07-18 Important change regarding Git Issue #8
    Build Guide: Important change regarding Git Issue #8, replaced Plastik 70 with Plastik 70 Super.
    Datasheet: Added maximum internal low power control signal Voltage, Updated Troubleshooting from Build Guide (July 18, 2025)
2025-08-06 accidentally deleted files from local repro
2025-08-06 Added v10 announcement to readme
2025-08-06 added v10 survey
2025-09-14 IMPORTANT NOTICE see #10 and fix in iBom
    IMPORTANT NOTICE: There was a complaint about the converter not being rules conform. Due to other personal priorities it might take some weeks to solve the addressed points. There is also the chance 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
    iBom: There were some components missing in the iBom for PCBA.
2025-09-19 updates LTspice sim
2025-09-28 fixed typo in schematic and README
2025-11-30 v10 Update, added Discord
2026-01-08 added comments to Spice Simulations
    Added note regards including missing models, cleaned up UVP/OVP simulation.
2026-01-29 README update
2026-01-30 Updated Documentation and Build guide
    See my comment regarding windings: https://github.com/Rootthecause/DCDC/discussions/4#discussioncomment-15645389
    This also includes other older updates in the build guide and documentation like the Note about the TL431 simulation model and fix for CAN Interferences If used with AMK Racing Kit.
2026-02-15 added build notes
2026-03-10 updated build notes, added primary winding video
2026-03-14 large DCDCv9-3r1.4 release update
    - Removed some tables in csv and ods format (xlsx preferred)
    - fixed issue #10 (waiting for approval)
    - added video of adhesive testing for ESG10C-20G
    - added video of primary and secondary winding
    - updated all documentation files incl. Scrutineering Support Presentation
    - updated transformer isolator part
2026-03-24 Fixed TL431 LCSC part number, added single winding holder for 12V version
2026-04-10 fixed R1, R71 wrong JLC component number for PCBAs see #13
2026-04-10 forgot crediting
2026-04-20 removed bug-causing comma in LTspice sim
    The Initial condition of the output capacitor was separated by a comma from it's capacitance value. This caused the simulation to fail on a Windows OS. As it also runs perfectly fine without the comm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
2026-05-11 Fixed U1 (see Build notes 260410), updated BOMs
2026-05-16 added MP4581 as replacement for MP4541
2026-05-17 made Build notes more visible
2026-06-09 testing new components for a v9-4. Not recommended for manufacturing !
    Replaced: D14, U1, U11, Q8, Q9, Q10, Q11
2026-06-09 testing new components for a v9-4. Not recommended for manufacturing!
    Replaced: D14, U1, U11, Q8, Q9, Q10, Q11
2026-06-10 Added ferrite bead to U3, enlarged SR FET cooling surface
2026-06-10 moved testpoint
2026-06-10 added PCBA BOM, added lots of JLC part numbers
2026-06-24 Updated teams on replica List
